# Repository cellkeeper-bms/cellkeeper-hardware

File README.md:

# CellKeeper BMS — v1.1

KiCad PCB design for the **CellKeeper Battery Management System**, a replacement BMS controller for battery packs using the isoSPI protocol. The main board fits the Tesla battery's penthouse: the pack's original harness, HV sense, shunt and BMB connectors plug into it, and it mounts on the original brackets.

Each ordered revision has a [release](https://github.com/cellkeeper-bms/cellkeeper-hardware/releases) with its Gerbers, JLCPCB BOM and CPL, schematic PDF, board PDF (3D views and 1:1 prints) and the enclosure print files. Rev 1.1 was ordered on 2026-10-28; work towards rev 1.2 is on the `rev1.2` branch.

## Overview

- **MCUs:** two Raspberry Pi RP2354B (dual Cortex-M33, 2 MB in-package flash): the main BMS controller and an independent supervisor, linked by UART. The supervisor also sees the isoSPI receive line and the E-stop input, and it alone enables the contactor drivers.
- **Current sensing:** TI INA228 (20-bit) on a galvanically isolated domain (ISO1540 I2C isolator, isolated 5 V DC-DC), also reading the shunt's temperature.
- **HV sensing:** 6 sense points (BAT±, LINK±, FC±) through 501:1 dividers into two ADS1115 ADCs: pack, link and output voltage, and the voltage across each contactor.
- **BMB communication:** transformer-isolated isoSPI master (SP3485 driver, AM26LV32 receiver, HM2113 transformer), Manchester-encoded by the RP2354's PIO.
- **CAN:** two ISO1050 interfaces: inverter CAN, isolated with its own DC-DC, on an RJ45 shared with the E-stop and aux lines; and inter-BMS CAN2 on a pass-through RJ45 pair (not isolated).
- **Contactors:** four low-side drivers (FC+, FC-, Link+, Link-): BSC0805LS MOSFETs and UCC27524 gate drivers, PWM'd by the firmware to economise the hold current. The contactor supply is sensed.
- **Supply:** 13–16 V logic and contactor inputs (separate, both sensed), TPS5430 5 V buck and 3.3 V LDO; chassis ground terminal.
- **HV battery:** 400 V nominal.
- **USB-C ×3:** BMS, supervisor, and HMI link. The HMI link is not for a computer: it powers an external ESP32 display (5 V 1 A) and carries its serial.
- **I/O:** E-stop input (optocoupler; jumper JP37 disables it), an extra opto input and two extra outputs, fast-charge contactor aux-contact inputs for weld detection, SX serial interface, and experimental PCS signals on jumpers.
- **Board revision** strap on GPIO47 (ADC7).

## Repository Contents

Three boards, each its own KiCad project. They share no copper: the hat and the precharge board
connect to the rest of the system by wires and lugs.

| Path | Description |
|------|-------------|
| `CellKeeper/` | Main controller board (`CellKeeper.kicad_pro`). Each ordered revision's Gerbers, BOM, CPL, schematic and board PDFs are on the [releases](https://github.com/cellkeeper-bms/cellkeeper-hardware/releases) page |
| `isoSPI-Hat/` | isoSPI hat for a Raspberry Pi Pico: SP3485 / AM26LV32 / HM2113 transformer to the BMB connector |
| `Precharge/` | Precharge board: six PTCs (three parallel strings of two) between M8 lugs, plus the HV system wiring diagram |
| `lib/` | Shared `CellKeeper_Local` symbol and footprint libraries and `CellKeeper.3dshapes` 3D models |
| `enclosure/` | 3D-printable case for the main board (build123d) |
| `graphics/` | Silkscreen artwork and README images |
| `python_scripts/` | README renders (`render_readme_images.py`), release files (`export_release_files.py`), 3D model generators |
| `docs/` | How to release a revision (`releasing.md`), README notes |

## Enclosure

A two-part printed case (base tray and lid) for the main board, generated by
`enclosure/cellkeeper_case.py`. It mounts in the penthouse on the original HVC brackets. The lid
carries the logo and connector labels, which can be printed as a contrasting-colour inlay, with
open tunnels over the LEDs. Ready-to-print STEP and STL files are attached to each
[release](https://github.com/cellkeeper-bms/cellkeeper-hardware/releases); running the script writes
them to `enclosure/output/print/`.
The board shows the case in KiCad's 3D viewer through the `ENC1` footprint.

## Safety

⚠️ This board interfaces with 400 V battery packs that can deliver **lethal** current. Only qualified personnel should work on high-voltage systems. This is a v1.1 development design — untested, no warranty, use at your own risk.

## Acknowledgments

- **Damien Maguire & Tom de Bree** — Original BATMan BMS software

## License

GPL-3.0 — see [LICENSE](LICENSE).

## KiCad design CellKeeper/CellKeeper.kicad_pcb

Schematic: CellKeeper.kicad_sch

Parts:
1/2V1, 3v1, 5V1: TP; BMS_Library__TestPoint_THTPad_D1.5mm_Drill1.0mm
BT5, BT6, BT7, BT8: ~100V Brick
C1, C14, C31: 680uF; Capacitor_THT__CP_Radial_D10.0mm_P5.00mm; Voltage 35V Polymer; JLCPCB Part # C46550429
C2, C10, C11, C13, C15, C16, C18, C22, C23, C28, C29, C30, C34, C35, C36, C54, C60, C73, C74, C89, C91, C104: 100nF; Capacitor_SMD__C_0603_1608Metric; JLCPCB Part # C14663
C3, C4, C6, C8, C17, C32, C66: 10uF; Capacitor_SMD__C_0805_2012Metric; Voltage 50V; JLCPCB Part # C440198
C5, C7, C12, C33, C37, C48, C49, C69: 22uF; Capacitor_SMD__C_0805_2012Metric; Voltage 25V X5R; JLCPCB Part # C45783
C9: 4.7uF; Capacitor_SMD__C_0603_1608Metric; JLCPCB Part # C19666
C19, C20, C41, C42, C67, C96, C97, C98, C99: 1uF; Capacitor_SMD__C_0603_1608Metric; JLCPCB Part # C15849
C21, C55, C116: 10uF; Capacitor_SMD__C_0805_2012Metric; Voltage 50V X5R; JLCPCB Part # C440198
C24, C25, C26, C27, C103: 100pF; Capacitor_SMD__C_0603_1608Metric; JLCPCB Part # C14858
C38, C43, C45, C52, C68, C72, C82, C87: 4.7u; RP2350_80QFN_minimal__C_0402_1005Metric_small_pads; JLCPCB Part # C23733
C39, C40, C70, C71: 15pF; Capacitor_SMD__C_0402_1005Metric; JLCPCB Part # C1548
C44, C46, C47, C50, C51, C53, C56, C58, C59, C61, C63, C65, C75, C83, C84, C85, C86, C88, C90, C92, C93, C100, C101, C102: 100n; Capacitor_SMD__C_0402_1005Metric; JLCPCB Part # C1525
C57, C105: 100n; Capacitor_SMD__C_0402_1005Metric; JLCPCB Part # C1525; not fitted
C62, C64, C76, C77, C78, C79, C80, C81: 100nf; Capacitor_SMD__C_0603_1608Metric; JLCPCB Part # C14663
C94, C95: 1nF; Capacitor_SMD__C_1206_3216Metric; JLCPCB Part # C9196
Cell1, Cell2, Cell3: Battery_Cell
D1, D2, D3, D4, D5, D6, D24, D25, D26, D28, D29, D30, D31: SMB6.8CA; Diode_SMD__D_SMB; JLCPCB Part # C78395
D7, D8, D14, D19, D32, D35, D36, D43, D48: Green; LED_SMD__LED_0805_2012Metric; JLCPCB Part # C2297
D9, D10, D27, D41, D46, D49: Red; LED_SMD__LED_0805_2012Metric; JLCPCB Part # C84256
D11, D12, D15, D16, D20, D23, D37, D38, D42, D44, D47, D50: SS54; Diode_SMD__D_SMA; JLCPCB Part # C22452
D13, D17, D22, D33, D34, D45: White; LED_SMD__LED_0805_2012Metric; JLCPCB Part # C34499
D18, D21, D39, D40: SMCJ33CA; Diode_SMD__D_SMC; JLCPCB Part # C224050
F3: Pyro Fuse
F4: 63A HV DC
FB1, FB3, FB5: 600R@100MHz; Inductor_SMD__L_0603_1608Metric_Pad1.05x0.95mm_HandSolder; JLCPCB Part # C1002
FB2: 120Ω@100MHz; Capacitor_SMD__C_0603_1608Metric; JLCPCB Part # C14709
FL1, FL2: SDCW3225S-2-102TF; BMS_Library__FILTER-SMD_4P-L3.2-W2.5-BL; JLCPCB Part # C192586
GND1: TP; BMS_Library__TestPoint_THTPad_D1.5mm_Drill1.0mm
GPIO44, GPIO45, GPIO46: TP; BMS_Library__TestPoint_THTPad_D1.5mm_Drill1.0mm
H1, H2, H7, H8: MountingHole_Pad; MountingHole__MountingHole_3.7mm; not fitted
H3, H4: MountingHole_Pad; MountingHole__MountingHole_5mm; not fitted
H5, H6: MountingHole_Pad
J1: WJ15EDGRC-3.81-04P-14-00A; BMS_Library__PhoenixContact_MC_1_5_4-G-3.81_1x04_P3.81mm_Ho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; JLCPCB Part # C7245
J2: T34008; BMS_Library__XFCN_T34008_M3_Terminal_Frame_PCB; JLCPCB Part # C481446
J3, J7: Screw_Terminal_01x04; BMS_Library__PhoenixContact_MC_1_5_4-G-3.81_1x04_P3.81mm_Ho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; JLCPCB Part # C7245; not fitted
J4, J5: 8P8C_LED_Shielded_x2; Connector_RJ__RJ45_HCTL_HC-RJ45-5JA-2-2-Y; JLCPCB Part # C3010546
J6: S44B-RAD1AK; BMS_Library__S44BRAD1AK; Mfr. # S44B-RAD1AK
J8, J16: Conn_01x03; Connector_PinHeader_2.54mm__PinHeader_1x03_P2.54mm_Vertical; not fitted
J9, J11, J19: USB_C_Receptacle_USB2.0_16P; BMS_Library__USB_C_Receptacle_HRO_TYPE-C-31-M-12; JLCPCB Part # C2765186
J10: 3.81P Screw Terminal; BMS_Library__PhoenixContact_MC_1_5_8-G-3.81_1x08_P3.81mm_Ho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; not fitted
J12, J22: Conn_02x10_Odd_Even; Connector_PinHeader_2.54mm__PinHeader_2x10_P2.54mm_Vertical; not fitted
J14: ZE05H-8DP-2H; BMS_Library__CONN_ZE05H-8DP-2H_HIR; MFR.Part # ZE05H-8DP-2H; JLCPCB Part # C17284895
J15: WJ15EDGRC-3.81-04P-14-00A; BMS_Library__PhoenixContact_MC_1_5_4-G-3.81_1x04_P3.81mm_Ho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; JLCPCB Part # C7245; not fitted
J17: OEM HV Sense Connector; BMS_Library__CONN_173864-1_TYC_Empty_Pins; MFR Part # 173864-1; JLCPCB Part # C573648
J18: 7.62mm Pitch Screw Terminal; Connector_Phoenix_GMSTB__PhoenixContact_GMSTBA_2_5_6-G-7_62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; not fitted
J20: OEM Connector; BMS_Library__CONN_SD-34912-001_02_MOL; MFR.Part # 349128020; JLCPCB Part # C587318
J21: 3.81P Screw Terminal; BMS_Library__PhoenixContact_MC_1_5_2-G-3.81_1x02_P3.81mm_Ho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; not fitted
JP3, JP4, JP7, JP8, JP9, JP12, JP13, JP14, JP16, JP17, JP18, JP19, JP20, JP21, JP22, JP23, JP24, JP27, JP28, JP29, JP30, JP31, JP32, JP33, JP34, JP35, JP37: 0r; BMS_Library__J_0603_jumper; JLCPCB Part # C21189; not fitted
JP5, JP6, JP10, JP11, JP15, JP36: 0r; BMS_Library__J_0603_jumper; JLCPCB Part # C21189
JP25, JP26, JP38, JP39: jumper-bridged; Jumper__SolderJumper-2_P1.3mm_Bridged_RoundedPad1.0x1.5mm
K5: Link Positive
K6: Link Negative
K7: FC Negative
K8: FC Positive
L1, L5: 6.8uh; Inductor_SMD__L_Changjiang_FXL0630; JLCPCB Part # C167221
L2, L3: 22uh 5.5A; Inductor_SMD__L_Changjiang_FXL1040; JLCPCB Part # C475917
L4, L6: 3.3uh; RP2350_80QFN_minimal__L_pol_2016; JLCPCB Part # C42411119
L7: Inverter
Q1, Q2, Q3, Q4: BSC0805LS; BMS_Library__TDSON-8_5x6_; JLCPCB Part # C534374
R1, R2, R11, R16, R29, R33, R35, R39, R40, R41, R96, R97, R98, R99, R100, R101, R140: 24k; Resistor_SMD__R_0603_1608Metric; JLCPCB Part # C23352
R3, R4, R13, R14, R15, R17, R19, R20, R21, R25, R28, R42, R50, R51, R52, R75, R84: 10k; Resistor_SMD__R_0603_1608Metric; JLCPCB Part # C25804
R5, R10, R18, R24, R34, R36, R151, R152: 100k; Resistor_SMD__R_0603_1608Metric; JLCPCB Part # C25803
R6: 25296nΩ
R7, R12, R37, R38: 33R; Resistor_SMD__R_0603_1608Metric; JLCPCB Part # C23140
R8, R9, R22, R23, R46, R47, R48, R49, R76, R133, R134, R141: 1k; Resistor_SMD__R_0603_1608Metric; JLCPCB Part # C21190
R26, R78, R155: 3.3k; Resistor_SMD__R_0402_1005Metric; JLCPCB Part # C25890
R27, R53, R55, R56, R74, R92, R94, R95, R129, R130, R131, R132, R135: 1k; Resistor_SMD__R_0402_1005Metric; JLCPCB Part # C11702
R30, R73, R86: 510r; Resistor_SMD__R_0603_1608Metric; JLCPCB Part # C23193
R31, R32: 120r; Resistor_SMD__R_1206_3216Metric; JLCPCB Part # C17909
R43, R44: 2.2k; Resistor_SMD__R_0603_1608Metric; JLCPCB Part # C4190
R45, R57, R66, R69, R72, R77, R79, R80, R81, R82, R83, R85, R89, R90, R138, R139, R143, R144, R153, R154: 5.1k; Resistor_SMD__R_0603_1608Metric; JLCPCB Part # C23186
R54, R68, R93, R126: 33r; Resistor_SMD__R_0402_1005Metric; JLCPCB Part # C25105
R58, R59, R60, R61, R62, R63, R64, R65: 18r
R67: 12.24R
R70, R71, R127, R128: 22R; Resistor_SMD__R_0402_1005Metric; JLCPCB Part # C25092
R87, R88: 220r; Resistor_SMD__R_0603_1608Metric; JLCPCB Part # C22962
R102, R103, R104, R105, R106, R107, R108, R109, R110, R111, R112, R113, R114, R115, R116, R117, R118, R119, R120, R121, R122, R123, R124, R125: 3M; Resistor_SMD__R_1206_3216Metric; JLCPCB Part # C488822
R136, R137: 47r; Resistor_SMD__R_0603_1608Metric; JLCPCB Part # C23182
R142: 100R; Resistor_SMD__R_0603_1608Metric; JLCPCB Part # C22775
R145, R146: 1M; Resistor_SMD__R_1206_3216Metric; JLCPCB Part # C17927
RevisionS1: TP; BMS_Library__TestPoint_THTPad_D1.5mm_Drill1.0mm
SW1, SW2, SW3, SW4: TS-1187A-B-A-B; Button_Switch_SMD__SW_Push_1P1T_XKB_TS-1187A; JLCPCB Part # C318884
TH1, TH2, TH3, TH4, TH5, TH6: B59451C1130B070; JLCPCB Part # C2762811
TP1, TP2, TP4, TP6, TP7, TP8, TP9, TP10, TP15, TP23, TP24, TP25, TP34, TP35, TP36, TP37, TP43, TP44, TP45: TestPoint_2Pole; BMS_Library__TestPoint_2Pads_Pitch2.54mm_Pad1.5_Drill1.0mm
TP3, TP5, TP11, TP12, TP13, TP14, TP16, TP17, TP18, TP19, TP20, TP21, TP22, TP26, TP27, TP28, TP29, TP30, TP31, TP32, TP33, TP38, TP39, TP40, TP41, TP49: TP; BMS_Library__TestPoint_THTPad_D1.5mm_Drill1.0mm
TP42: TestPoint_2Pole; BMS_Library__TestPoint_2Pads_Pitch2.54mm_Pad1.5_Drill1.0mm; not fitted
TR1: HM2113ZNLT; BMS_Library__HM2113ZNLT; JLCPCB Part # C5730533
U1, U11: UCC27524DR; Package_SO__SOIC-8_3.9x4.9mm_P1.27mm; JLCPCB Part # C465729
U3: TPS5430DDAR; Package_SO__TI_SO-PowerPAD-8_ThermalVias; LCSC Part C9864
U4, U15: F0505S-1WR3; BMS_Library__H0505S-1WR2; JLCPCB Part # C7465182
U5, U10: ISO1050DUB; Package_SO__SOP-8_6.62x9.15mm_P2.54mm; LCSC Part # C16428
U6, U7, U8, U9, U12, U13: LTV-217-B-G; Package_SO__SSOP-4_4.4x2.6mm_P1.27mm; JLCPCB Part # C115450
U14, U20: RP2354B; RP2350_80QFN_minimal__RP2350-QFN-80-1EP_10x10_P0.4mm_EP3.4x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; JLCPCB Part # C39843328
U16: ISO1540; Package_SO__SOIC-8_3.9x4.9mm_P1.27mm; JLCPCB Part # C179739
U17: INA228; Package_SO__TSSOP-10_3x3mm_P0.5mm; JLCPCB Part # C5214669
U18, U19: ADS1115; Package_SO__TSSOP-10_3x3mm_P0.5mm; LCSC Part # C37593
U21: SP3485EN-L/TR; Package_SO__SOIC-8_3.9x4.9mm_P1.27mm; JLCPCB Part # C8963
U22: AM26LV32EIDR; Package_SO__SOIC-16_3.9x9.9mm_P1.27mm; JLCPCB Part # C527448
U23, U24: W25Q16JVUXIQ; Winbond_USON-8-1EP_3x2mm_P0.5mm_EP0.2x1.6mm; JLCPCB Part # C2843335; not fitted
U25, U26: TLV1117LV33DCYR; Package_TO_SOT_SMD__SOT-223-3_TabPin2; JLCPCB Part # C15578
Y1, Y2: ABM8-272-T3; Crystal__Crystal_SMD_3225-4Pin_3.2x2.5mm; JLCPCB Part # C20625731

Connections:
3.3V Sense: C22.2, R20.2, R21.1, U14.49 (GPIO40_ADC0)
5V Sense: C36.2, R41.2, R42.1, U14.52 (GPIO41_ADC1)
+1V1: C43.1, C44.1, C46.1, C47.1, L4.1, U14.10 (DVDD), U14.32 (DVDD), U14.51 (DVDD), U14.65 (VREG_FB)
+1V1_2: C72.1, C75.1, C83.1, C84.1, L6.1, U20.10 (DVDD), U20.32 (DVDD), U20.51 (DVDD), U20.65 (VREG_FB)
+3.3V: C9.2, C10.1, C11.1, C38.1, C50.1, C51.1, C53.1, C56.1, C57.1, C58.1, C59.1, C61.1, C63.1, C65.1, C66.2, C68.1, C85.1, C86.1, C88.1, C89.1, C90.1, C91.2, C92.1, C93.1, C100.1, C101.1, C102.1, C105.1, D7.2 (A), D9.2 (A), D41.2 (A), D43.2 (A), FB5.1, J3.1, J12.5, J12.7, J12.9, J22.5, J22.7, J22.9, JP35.2, R2.1, R4.1, R15.1, R20.1, R28.1, R29.1, R54.2, R57.1, R66.1, R68.2, R75.1, R89.1, R90.1, R93.2, R126.2, R135.1, TP4.2, U5.1 (VCC1), U6.4, U7.4, U10.1 (VCC1), U12.4, U13.4, U14.5 (IOVDD), U14.15 (IOVDD), U14.24 (IOVDD), U14.29 (IOVDD), U14.41 (IOVDD), U14.50 (IOVDD), U14.60 (IOVDD), U14.64 (VREG_VIN), U14.68 (USB_OTP_VDD), U14.69 (QSPI_IOVDD), U14.76 (IOVDD), U16.1 (VCC1), U20.5 (IOVDD), U20.15 (IOVDD), U20.24 (IOVDD), U20.29 (IOVDD), U20.41 (IOVDD), U20.50 (IOVDD), U20.60 (IOVDD), U20.64 (VREG_VIN), U20.68 (USB_OTP_VDD), U20.69 (QSPI_IOVDD), U20.76 (IOVDD), U21.8 (VCC), U22.4 (G), U22.16 (VDD), U23.8 (VCC), U24.8 (VCC), U25.2 (VO)
+3.3VSen: 3v1.1 (1_1), C67.2, C73.2, C74.2, FB5.2, R87.1, U18.8 (VDD), U19.1 (ADDR), U19.8 (VDD)
+5V: C2.2, C3.2, C7.2, C18.2, C29.2, C31.1, C32.2, C33.2, C37.2, C41.2, C42.2, C48.2, D50.2 (A), FB2.2, J12.1, J12.3, J22.1, J22.3, L1.2, L3.1, L5.2, R26.1, R35.1, R41.1, TP9.2, U1.6 (V_{DD}), U10.8 (VCC2), U11.6 (V_{DD}), U12.1, U13.1
+LDO_IN: C5.2, D44.1 (K), D47.1 (K), D50.1 (K), U25.3 (VI)
/Blue: J4.4, JP15.2, JP16.1, JP18.1
/Brown: J4.8, JP19.2, JP20.1, JP23.1
/CAN2 H: C26.2, D30.2 (A2), FL2.2, J5.4, J5.16, R32.2, TP8.2
/CAN2 L: C27.1, D31.1 (A1), FL2.3, J5.5, J5.17, JP5.1, TP8.1
/CAN 5V: 5V1.1 (1_1), C28.2, FB1.2, R22.2, R30.1, R33.1, R43.2, U5.8 (VCC2)
/CAN H: C24.2, D28.2 (A2), FL1.2, JP3.1, JP7.1, JP9.1, JP13.1, JP15.1, JP19.1, JP21.1, JP27.1, JP36.1, TP7.2
/CAN L: C25.1, D29.1 (A1), FL1.3, JP4.2, JP8.2, JP10.2, JP14.2, JP16.2, JP20.2, JP22.2, JP28.2, R31.1, TP7.1
/Contactor_Input: D1.2 (A2), D11.2 (A), D12.2 (A), J1.3
/FC-CTR-NEG-AUX-D: J6.17, J7.2, R47.1
/FC-CTR-POS-AUX-D: J6.18, J7.1, R46.1
/FC-Neg-Jumper: C35.2, D36.1 (K), D38.2 (A), D40.2 (A2), JP25.1 (A), JP26.1 (A), Q4.5 (D)
/FC-Pos-Jumper: C13.2, D14.1 (K), D16.2 (A), D18.2 (A2), JP38.1 (A), JP39.1 (A), Q1.5 (D)
/GPIO0: R74.2, U14.77 (GPIO0)
/GPIO25: R85.1, U14.26 (GPIO25)
/GPIO44_ADC4: GPIO44.1 (1_1), U14.55 (GPIO44_ADC4)
/GPIO45_ADC5: GPIO45.1 (1_1), U14.56 (GPIO45_ADC5)
/GPIO46_ADC6: GPIO46.1 (1_1), U14.57 (GPIO46_ADC6)
/GPIO47_ADC7: R75.2, R76.1, RevisionS1.1 (1_1), U14.58 (GPIO47_ADC7)
/Grn: J4.6, JP7.2, JP8.1, JP11.1
/Logic_Input: D4.2 (A2), D15.2 (A), J1.4, R151.2
/MCU2_GPIO0: R135.2, U20.77 (GPIO0)
/MCU2_GPIO1: R131.2, U20.78 (GPIO1)
/MCU2_GPIO2: R132.2, U20.79 (GPIO2)
/MCU2_GPIO4: J22.4, U20.1 (GPIO4)
/MCU2_GPIO5: J22.6, U20.2 (GPIO5)
/MCU2_GPIO6: J22.8, R133.1, U20.3 (GPIO6)
/MCU2_GPIO7: J22.10, U20.4 (GPIO7)
/MCU2_GPIO8: J22.12, R134.1, U20.6 (GPIO8)
/MCU2_GPIO9: J22.14, U20.7 (GPIO9)
/MCU2_GPIO10: J22.16, U20.8 (GPIO10)
/MCU2_GPIO12: J22.20, U20.11 (GPIO12)
/MCU2_GPIO13: U20.12 (GPIO13)
/MCU2_GPIO14: R140.1, R141.1, U20.13 (GPIO14)
/MCU2_GPIO15: U20.14 (GPIO15)
/MCU2_GPIO16: U20.16 (GPIO16)
/MCU2_GPIO17: U20.17 (GPIO17)
/MCU2_GPIO18: U20.18 (GPIO18)
/MCU2_GPIO19: U20.19 (GPIO19)
/MCU2_GPIO20: U20.20 (GPIO20)
/MCU2_GPIO21: U20.21 (GPIO21)
/MCU2_GPIO22: U20.22 (GPIO22)
/MCU2_GPIO23: U20.23 (GPIO23)
/MCU2_GPIO24: U20.25 (GPIO24)
/MCU2_GPIO25: R143.1, U20.26 (GPIO25)
/MCU2_GPIO26: U20.27 (GPIO26)
/MCU2_GPIO27: U20.28 (GPIO27)
/MCU2_GPIO33: U20.42 (GPIO33)
/MCU2_GPIO34: U20.43 (GPIO34)
/MCU2_GPIO35: U20.44 (GPIO35)
/MCU2_GPIO36: U20.45 (GPIO36)
/MCU2_GPIO37: U20.46 (GPIO37)
/MCU2_GPIO38: R129.2, U20.47 (GPIO38)
/MCU2_GPIO39: R130.2, U20.48 (GPIO39)
/Orange: J4.2, JP21.2, JP22.1, JP24.1
/PH: C16.1, D23.1 (K), L3.2, U3.8 (PH)
/RUN: R56.2, SW2.2, TP14.1 (1_1)
/SWCLK: J8.1, U14.33 (SWCLK)
/SWD: J8.3, U14.34 (SWD)
/Serial API 5V Diode: D42.1 (K), J9.A4 (VBUS), J9.A9 (VBUS), J9.B4 (VBUS), J9.B9 (VBUS), TP13.1 (1_1)
/Serial API RX: J9.A7 (D-), J9.B7 (D-), R48.1, R50.2, TP10.1
/Serial API TX: J9.A6 (D+), J9.B6 (D+), R49.1, TP10.2
/USB2_D+: J19.A6 (D+), J19.B6 (D+), R127.1, TP39.1 (1_1)
/USB2_D-: J19.A7 (D-), J19.B7 (D-), R128.1, TP40.1 (1_1)
/USB_D+: J11.A6 (D+), J11.B6 (D+), R70.1, TP20.1 (1_1)
/USB_D-: J11.A7 (D-), J11.B7 (D-), R71.1, TP21.1 (1_1)
/VREG2_AVDD: C82.1, R93.1, U20.61 (VREG_AVDD)
/VREG2_LX: L6.2, U20.63 (VREG_LX)
/VREG_AVDD: C45.1, R54.1, U14.61 (VREG_AVDD)
/VREG_LX: L4.2, U14.63 (VREG_LX)
/V_cont1: C8.2, D11.1 (K), D12.1 (K), L2.2
/Wht-Blue: J4.5, JP9.2, JP10.1, JP12.1
/Wht-Brown: J4.7, JP13.2, JP14.1, JP17.1
/Wht-Grn: J4.3, JP3.2, JP4.1, JP6.1
/Wht-Org: J4.1, JP27.2, JP28.1, JP29.1
/iso+: C96.1, C99.1, C103.2, R136.2, R142.1, TP42.1, TR1.1 (TD-)
/iso-: C97.1, C98.1, C103.1, R137.2, R142.2, TP42.2, TR1.3 (TD+)
Batt Negative: J17.1, J18.6, R121.2
Batt Positive: J17.10, J18.1, R120.2
C FC-Neg (GND): J6.37, J10.2, JP25.2 (B), JP26.2 (B)
C FC-Pos (GND): J6.36, J10.4, JP38.2 (B), JP39.2 (B)
C Neg (GND): C34.2, D35.1 (K), D37.2 (A), D39.2 (A2), J6.42, J10.6, Q3.5 (D)
C Pos (GND): C15.2, D19.1 (K), D20.2 (A), D21.2 (A2), J6.41, J10.8, Q2.5 (D)
CAN2 Rx: D8.1 (K), J12.6, TP2.1, U10.2 (RXD), U14.2 (GPIO5)
CAN2 Tx: D10.1 (K), J12.4, TP2.2, U10.3 (TXD), U14.1 (GPIO4)
CAN Rx: R1.2, TP1.1, U5.2 (RXD), U14.20 (GPIO20)
CAN Tx: R3.2, TP1.2, U5.3 (TXD), U14.19 (GPIO19)
CTR-FC-NEG: R83.1, U11.4 (INB), U14.14 (GPIO15)
CTR-FC-Pos: R82.1, U1.4 (INB), U14.16 (GPIO16)
CTR-LNK-NEG: R81.1, U11.2 (INA), U14.17 (GPIO17)
CTR-LNK-POS: R77.1, U1.2 (INA), U14.18 (GPIO18)
CTR_EN: R141.2, R144.1, U1.1 (ENA), U1.8 (ENB), U11.1 (ENA), U11.8 (ENB)
Emergency Stop: J12.18, J22.18, R13.2, U6.3, U14.9 (GPIO11), U20.9 (GPIO11)
Extra Input: J12.20, R14.2, U7.3, U14.11 (GPIO12)
Extra Output 1: R8.1, U14.12 (GPIO13)
Extra Output 2: R9.1, U14.13 (GPIO14)
FC Negative: J17.4, J18.4, R123.2
FC Positive: J17.7, J18.3, R122.2
FC-CTR-NEG-AUX: J12.16, R52.2, U13.3, U14.8 (GPIO10)
FC-CTR-POS-AUX: J12.14, R51.2, U12.3, U14.7 (GPIO9)
GND: C1.2, C2.1, C3.1, C4.1, C5.1, C6.1, C7.1, C8.1, C9.1, C10.2, C11.2, C12.1, C13.1, C14.2, C15.1, C17.1, C18.1, C22.1, C23.1, C26.1, C27.2, C29.1, C30.1, C31.2, C32.1, C33.1, C34.1, C35.1, C36.1, C37.1, C38.2, C39.2, C40.2, C43.2, C44.2, C45.2, C46.2, C47.2, C48.1, C49.1, C50.2, C51.2, C52.2, C53.2, C56.2, C57.2, C58.2, C59.2, C61.2, C63.2, C65.2, C66.1, C67.1, C68.2, C69.1, C70.2, C71.2, C72.2, C73.1, C74.1, C75.2, C82.2, C83.2, C84.2, C85.2, C86.2, C87.2, C88.2, C89.2, C90.2, C91.1, C92.2, C93.2, C100.2, C101.2, C102.2, C104.1, C105.2, D3.1 (A1), D6.1 (A1), D13.1 (K), D17.1 (K), D18.1 (A1), D21.1 (A1), D22.1 (K), D23.2 (A), D26.1 (A1), D30.1 (A1), D31.2 (A2), D34.1 (K), D39.1 (A1), D40.1 (A1), D46.1 (K), D48.1 (K), D49.1 (K), GND1.1 (1_1), J1.1, J1.2, J2.1 (Pin_1_1), J3.4, J5.3, J5.6, J5.15, J5.18, J5.SH, J6.3, J6.4, J6.30, J7.3, J7.4, J8.2, J9.A1 (GND), J9.A12 (GND), J9.B1 (GND), J9.B12 (GND), J9.SH (SHIELD), J11.A1 (GND), J11.A12 (GND), J11.B1 (GND), J11.B12 (GND), J11.SH (SHIELD), J12.11, J12.13, J12.15, J12.17, J12.19, J16.2, J19.A1 (GND), J19.A12 (GND), J19.B1 (GND), J19.B12 (GND), J19.SH (SHIELD), J22.11, J22.13, J22.15, J22.17, J22.19, Q1.1 (S), Q1.2 (S), Q1.3 (S), Q2.1 (S), Q2.2 (S), Q2.3 (S), Q3.1 (S), Q3.2 (S), Q3.3 (S), Q4.1 (S), Q4.2 (S), Q4.3 (S), R5.1, R10.1, R13.1, R14.1, R19.2, R21.2, R25.2, R27.2, R34.1, R36.1, R42.2, R51.1, R52.1, R74.1, R76.2, R77.2, R79.1, R80.1, R81.2, R82.2, R83.2, R88.2, R138.1, R139.1, R144.2, R146.1, R153.2, R154.2, SW1.1, SW2.1, SW3.1, SW4.1, TP3.1 (1_1), TP4.1, TP9.1, TP11.1 (1_1), TP16.1 (1_1), TP19.1 (1_1), TP23.1, TP24.1, TP38.1 (1_1), TP43.1, TP44.1, U1.3 (GND), U3.6 (GND), U3.9 (PowerPAD), U4.2 (-Vin), U5.4 (GND1), U8.2, U9.2, U10.4 (GND1), U10.5 (GND2), U11.3 (GND), U14.62 (VREG_PGND), U14.81 (GND), U15.2 (-Vin), U16.4 (GND1), U18.1 (ADDR), U18.3 (GND), U19.3 (GND), U20.62 (VREG_PGND), U20.81 (GND), U21.2 (~RE), U21.5 (GND), U22.8 (GND), U22.12 (~G), U23.4 (GND), U24.4 (GND), U25.1 (GND), Y1.2, Y1.4, Y2.2, Y2.4
GND CAN: C21.1, C24.1, C25.2, C28.1, D28.1 (A1), D29.2 (A2), D33.1 (K), J4.19, J4.SH, JP6.2, JP11.2, JP12.2, JP17.2, JP18.2, JP23.2, JP24.2, JP29.2, JP37.2, R30.2, TP5.1 (1_1), U4.5 (-Vout), U5.5 (GND2)
GND Shunt NTC -: C54.1, C55.1, C60.1, C64.1, C116.1, D45.1 (K), J14.1, J14.3, J15.2, R73.2, R86.2, TP17.1 (1_1), U15.5 (-Vout), U16.5 (GND2), U17.1 (A1), U17.2 (A0), U17.7 (GND), U26.1 (GND)
HMI Serial RX: R48.2, R130.1, U14.48 (GPIO39)
HMI Serial TX: R45.2, R49.2, R129.1, U14.47 (GPIO38)
I2C SCL Shunt: R57.2, TP15.2, U14.21 (GPIO21), U16.3 (SCL1)
I2C SCL Vsense: R90.2, TP25.2, U14.23 (GPIO23), U18.10 (SCL), U19.10 (SCL)
I2C SDA Shunt: R66.2, TP15.1, U14.25 (GPIO24), U16.2 (SDA1)
I2C SDA Vsense: R89.2, TP25.1, U14.22 (GPIO22), U18.9 (SDA), U19.9 (SDA)
IsoSPI RX Debug: TP24.2, U14.39 (GPIO31)
IsoSPI RX Debug 2: TP43.2, U20.39 (GPIO31)
IsoSPI RX H: TP35.1, U14.36 (GPIO28), U20.36 (GPIO28), U22.5 (2Y)
IsoSPI RX L: TP35.2, U14.37 (GPIO29), U20.37 (GPIO29), U22.3 (1Y)
IsoSPI TX Data: TP34.2, U14.28 (GPIO27), U21.4 (DI)
IsoSPI TX En: TP34.1, U14.27 (GPIO26), U21.3 (DE)
IsoSPI+: J20.1, J21.1, TR1.4 (TX+)
IsoSPI-: J20.2, J21.2, TR1.6 (TX-)
Link Negative: J17.13, J18.5, R124.2
Link Positive: J17.22, J18.2, R125.2
MAIN-SUP TX/RX: R131.1, TP36.1, U14.79 (GPIO2)
MAX RX: J12.8, R133.2, U14.3 (GPIO6), U22.13 (4Y)
unnamed: BT5.1 (+), K5.14
unnamed: BT5.2 (-), BT6.1 (+)
unnamed: BT6.2 (-), R6.1
unnamed: BT7.1 (+), F3.1
unnamed: BT7.2 (-), BT8.1 (+)
unnamed: BT8.2 (-), K6.14
unnamed: C19.1, J4.20, J4.21, JP37.1, U6.2
unnamed: C19.2, R22.1, U6.1
unnamed: C20.1, J4.14, J4.23, U7.2
unnamed: C20.2, R23.1, U7.1
unnamed: C40.1, R53.2, Y1.3
unnamed: C41.1, R46.2, U12.2
unnamed: C42.1, R47.2, U13.2
unnamed: C71.1, R92.2, Y2.3
unnamed: C94.1, TP37.2
unnamed: C95.1, TP37.1
unnamed: Cell1.1 (+), R58.1, R59.1
unnamed: Cell1.2 (-), Cell2.1 (+), R60.1, R61.1
unnamed: Cell2.2 (-), Cell3.1 (+), R62.1, R63.1
unnamed: Cell3.2 (-), R64.1, R65.1
unnamed: D1.1 (A1), D2.2 (A2)
unnamed: D2.1 (A1), D3.2 (A2)
unnamed: D4.1 (A1), D5.2 (A2)
unnamed: D5.1 (A1), D6.2 (A2)
unnamed: D7.1 (K), R1.1
unnamed: D8.2 (A), R2.2
unnamed: D9.1 (K), R3.1
unnamed: D10.2 (A), R4.2
unnamed: D13.2 (A), R151.1
unnamed: D14.2 (A), R11.2
unnamed: D17.2 (A), R15.2
unnamed: D19.2 (A), R16.2
unnamed: D22.2 (A), R152.1
unnamed: D24.1 (A1), D25.2 (A2)
unnamed: D25.1 (A1), D26.2 (A2)
unnamed: D27.2 (A), R28.2
unnamed: D32.2 (A), R29.2
unnamed: D33.2 (A), R33.2
unnamed: D34.2 (A), R35.2
unnamed: D35.2 (A), R39.2
unnamed: D36.2 (A), R40.2
unnamed: D41.1 (K), R45.1
unnamed: D42.2 (A), FB2.1
unnamed: D43.1 (K), R50.1
unnamed: D44.2 (A), J11.A4 (VBUS), J11.A9 (VBUS), J11.B4 (VBUS), J11.B9 (VBUS), R78.2, TP22.1 (1_1)
unnamed: D45.2 (A), R17.2
unnamed: D46.2 (A), R85.2
unnamed: D47.2 (A), J19.A4 (VBUS), J19.A9 (VBUS), J19.B4 (VBUS), J19.B9 (VBUS), R155.2, TP41.1 (1_1)
unnamed: D48.2 (A), R140.2
unnamed: D49.2 (A), R143.2
unnamed: F3.2, R6.4
unnamed: H5.1, K6.13, K7.14, TH1.1, TH2.1, TH3.1
unnamed: H6.1, K7.13, L7.2, TH4.2, TH5.2, TH6.2
unnamed: J4.13, R23.2, R44.2
unnamed: J4.15, U9.4
unnamed: J4.16, U8.3
unnamed: J4.17, U8.4
unnamed: J4.18, U9.3
unnamed: J4.22, R43.1
unnamed: J4.24, R44.1
unnamed: J6.1, JP30.2
unnamed: J6.2, JP31.2
unnamed: J6.5, JP32.2
unnamed: J6.6, JP33.2
unnamed: J6.15, JP34.2
unnamed: J6.29, JP35.1
unnamed: J11.A5 (CC1), R79.2
unnamed: J11.B5 (CC2), R80.2
unnamed: J16.1, U20.33 (SWCLK)
unnamed: J16.3, U20.34 (SWD)
unnamed: J19.A5 (CC1), R138.2
unnamed: J19.B5 (CC2), R139.2
unnamed: JP5.2, R32.1
unnamed: JP36.2, R31.2
unnamed: K5.13, K8.14
unnamed: K8.13, L7.1
unnamed: Q1.4 (G), R7.2
unnamed: Q2.4 (G), R12.2
unnamed: Q3.4 (G), R37.2
unnamed: Q4.4 (G), R38.2
unnamed: R8.2, U8.1
unnamed: R9.2, U9.1
unnamed: R55.2, SW1.2, TP12.1 (1_1)
unnamed: R58.2, R59.2
unnamed: R60.2, R61.2, R67.2
unnamed: R62.2, R63.2, R67.1
unnamed: R64.2, R65.2
unnamed: R94.2, SW3.2, TP26.1 (1_1)
unnamed: R95.2, SW4.2, TP30.1 (1_1)
unnamed: R102.2, R108.1
unnamed: R103.2, R109.1
unnamed: R104.2, R110.1
unnamed: R105.2, R111.1
unnamed: R106.2, R112.1
unnamed: R107.2, R113.1
unnamed: R108.2, R114.1
unnamed: R109.2, R115.1
unnamed: R110.2, R116.1
unnamed: R111.2, R117.1
unnamed: R112.2, R118.1
unnamed: R113.2, R119.1
unnamed: R114.2, R120.1
unnamed: R115.2, R121.1
unnamed: R116.2, R122.1
unnamed: R117.2, R123.1
unnamed: R118.2, R124.1
unnamed: R119.2, R125.1
unnamed: R145.1, R146.2
unnamed: TH1.2, TH4.1
unnamed: TH2.2, TH5.1
unnamed: TH3.2, TH6.1
unnamed: C104.2, TR1.2 (C_TD)
unnamed: R145.2, TR1.5 (C_TX)
unnamed: R10.2, R12.1, U1.7 (OUTA)
unnamed: R5.2, R7.1, U1.5 (OUTB)
unnamed: C16.2, U3.1 (BOOT)
unnamed: R26.2, R27.1, U3.4 (VSENSE)
unnamed: C12.2, L1.1, U4.1 (+Vin)
unnamed: C21.2, FB1.1, U4.7 (+Vout)
unnamed: FL1.1, U5.7 (CANH)
unnamed: FL1.4, U5.6 (CANL)
unnamed: FL2.1, U10.7 (CANH)
unnamed: FL2.4, U10.6 (CANL)
unnamed: R34.2, R37.1, U11.7 (OUTA)
unnamed: R36.2, R38.1, U11.5 (OUTB)
unnamed: C52.1, R68.1, U14.59 (ADC_AVDD)
unnamed: U14.71 (QSPI_SCLK), U23.6 (CLK)
unnamed: U14.72 (QSPI_SD0), U23.5 (DI/IO_{0})
unnamed: U14.74 (QSPI_SD1), U23.2 (DO/IO_{1})
unnamed: U14.73 (QSPI_SD2), U23.3 (~WP/IO_{2})
unnamed: U14.70 (QSPI_SD3), U23.7 (~HOLD/~RESET/IO_{3})
unnamed: R55.1, U14.75 (QSPI_SS), U23.1 (~CS)
unnamed: R56.1, U14.35 (RUN)
unnamed: R71.2, U14.66 (USB_DM)
unnamed: R70.2, U14.67 (USB_DP)
unnamed: C39.1, U14.30 (XIN), Y1.1
unnamed: R53.1, U14.31 (XOUT)
unnamed: C49.2, L5.1, U15.1 (+Vin)
unnamed: C55.2, FB3.1, U15.7 (+Vout)
unnamed: R72.2, U16.6 (SCL2), U17.5 (SCL)
unnamed: R69.2, U16.7 (SDA2), U17.4 (SDA)
unnamed: C76.2, R96.1, R102.1, TP31.1 (1_1), U18.4 (AIN0), U19.6 (AIN2)
unnamed: C77.1, R97.2, R103.1, TP29.1 (1_1), U18.5 (AIN1)
unnamed: C78.2, R98.1, R104.1, TP33.1 (1_1), U18.6 (AIN2), U19.5 (AIN1)
unnamed: C79.1, R99.1, R105.1, TP27.1 (1_1), U18.7 (AIN3)
unnamed: C80.2, R100.1, R106.1, TP32.1 (1_1), U19.4 (AIN0)
unnamed: C81.1, R101.1, R107.1, TP28.1 (1_1), U19.7 (AIN3)
unnamed: C87.1, R126.1, U20.59 (ADC_AVDD)
unnamed: U20.71 (QSPI_SCLK), U24.6 (CLK)
unnamed: U20.72 (QSPI_SD0), U24.5 (DI/IO_{0})
unnamed: U20.74 (QSPI_SD1), U24.2 (DO/IO_{1})
unnamed: U20.73 (QSPI_SD2), U24.3 (~WP/IO_{2})
unnamed: U20.70 (QSPI_SD3), U24.7 (~HOLD/~RESET/IO_{3})
unnamed: R94.1, U20.75 (QSPI_SS), U24.1 (~CS)
unnamed: R95.1, U20.35 (RUN)
unnamed: R128.2, U20.66 (USB_DM)
unnamed: R127.2, U20.67 (USB_DP)
unnamed: C70.1, U20.30 (XIN), Y2.1
unnamed: R92.1, U20.31 (XOUT)
unnamed: R136.1, U21.6 (A)
unnamed: R137.1, U21.7 (B)
unnamed: C96.2, U22.2 (1A)
unnamed: C97.2, U22.1 (1B)
unnamed: C98.2, U22.6 (2A)
unnamed: C99.2, U22.7 (2B)
unnamed: C94.2, U22.14 (4A)
unnamed: C95.2, U22.15 (4B)
PCS Charge: JP34.1, U14.46 (GPIO37)
PCS DCDC: JP30.1, U14.42 (GPIO33)
PCS Enable: JP31.1, U14.45 (GPIO36)
PCS IPC CAN RX: JP32.1, U14.44 (GPIO35)
PCS IPC CAN TX: JP33.1, U14.43 (GPIO34)
SUP-MAIN TX/RX: R132.1, TP36.2, U14.78 (GPIO1)
SX Serial RX: D32.1 (K), J3.3, J12.12, R134.2, TP6.2, U14.6 (GPIO8)
SX Serial TX: D27.1 (K), J3.2, J12.10, TP6.1, U14.4 (GPIO7)
Shunt Midpoint: J14.8
Shunt NTC +: C64.2, J14.7, J15.1, R84.1, U17.8 (Vbus)
Shunt Passive +: J14.6
Shunt Sense +: C62.2, J14.5, J15.3, TP45.2, U17.10 (Vin+)
Shunt Sense -: C62.1, J14.4, J15.4, TP45.1, U17.9 (Vin-)
Shunt_3V3: C54.2, C60.2, C116.2, R17.1, R69.1, R72.1, R84.2, TP49.1 (1_1), U16.8 (VCC2), U17.6 (VS), U26.2 (VO)
Shunt_5V: FB3.2, R73.1, R86.1, TP18.1 (1_1), U26.3 (VI)
Snooper Debug: TP23.2, U14.40 (GPIO32)
Snooper Debug 2: TP44.2, U20.40 (GPIO32)
VBUS Detect USB1: J12.2, R78.1, R153.1, U14.80 (GPIO3)
VBUS Detect USB2: J22.2, R154.1, R155.1, U20.80 (GPIO3)
VContactor Sense: C30.2, R24.1, R25.1, U14.54 (GPIO43_ADC3)
VSenHalf: 1/2V1.1 (1_1), C69.2, C76.1, C77.2, C78.1, C79.2, C80.1, C81.2, R87.2, R88.1, R96.2, R97.1, R98.2, R99.2, R100.2, R101.2
V_{Contactor}: C14.1, C17.2, D16.1 (K), D20.1 (K), D24.2 (A2), D37.1 (K), D38.1 (K), J6.33, J6.34, J6.35, J6.43, J10.1, J10.3, J10.5, J10.7, L2.1, R11.1, R16.1, R24.2, R39.1, R40.1, R152.2
V_{in}: C1.1, C4.2, C6.2, D15.1 (K), R18.2, U3.7 (VIN)
Vin Logic Sense: C23.2, R18.1, R19.1, U14.53 (GPIO42_ADC2)

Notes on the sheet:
all JLC basic components
Overall HV Battery System Diagram
3.3V 1A LDO Supply
GPIO3 - GPIO12 on NC header
external NC switch for estop, or jumper to disable.
Not tested as of now
I2C ADDR: 0x49
Aux Input 3-5V limited by resistor dissipation for higher input voltage use external series resistor
FC Negative Contactor
Would be cool if it alternates with main
BMB side xfmr center tap has no connection reference to ground to prevent ESD
Use 3v3 so no logic translation necessary.
TX must be on this pin
GND to battery chassis
unused inputs left floating - internal bias
3A max output - 3.3V draws from this rail
1.122V
1.52V
PTC max current ~10A Under 1S charge time expected
100k input impedance 0.14mA typical ADC usage
Gate driver has internal 200k pullup, 2x in parallel = 100k pullup must pull down to always start in off state.
DIY connector
MCU Identification
In tesla packs the shunt is at the mid point of the pack and always live!
second ADS1115: 0-1 linkneg - outpos 0-3 linkneg - linkpos <- link voltage 1-3 outpos - linkpos <- voltage across FC pos contactor 2-3 batpos - linkpos <- voltage across battery pos contactor
Supervisor MCU
5V powers exteral ESP32 LCD also
FC Positive Contactor
Cells to Positive Link Contactor
close to MCU
Aux contacts inside of the FC contactors used to check for welding with or without energizing
Extra GPIO
API TTL RS232 HMI Interface
Redundant connectors
Galvanically Isolated Area
isoSPI Transceiver
Inductor Alternate Parts (untested) APS201610M3R3F C48783272 MHT201610SG-3R3M H C49435043
Shunt Current Sense
Redundant connectors only one used at a time
3.77V

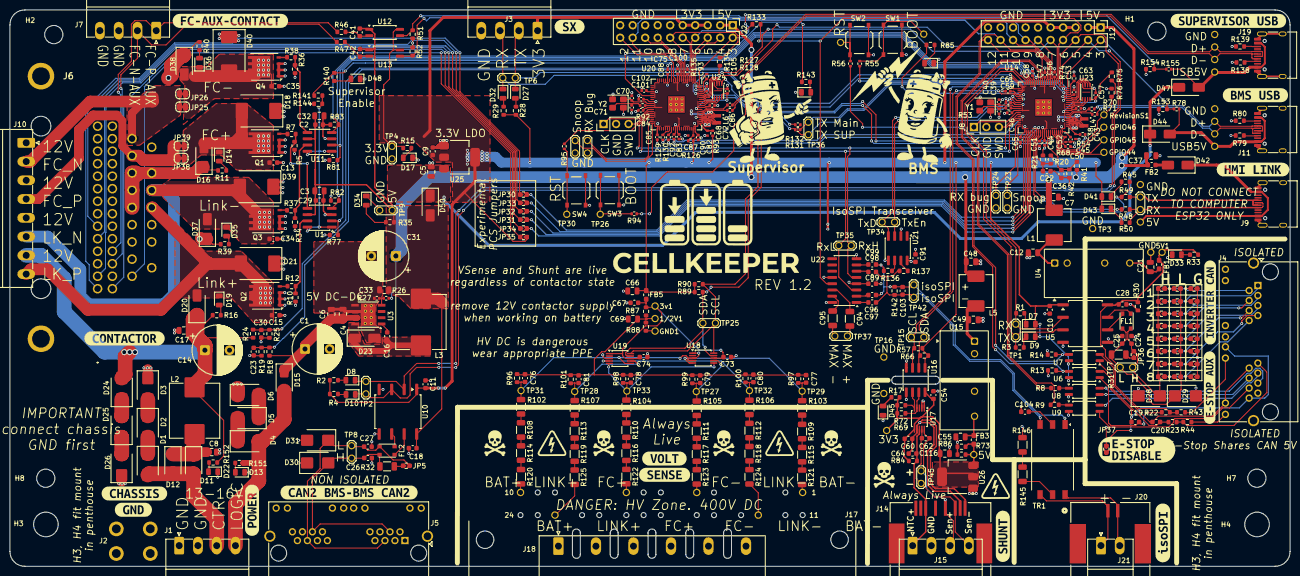
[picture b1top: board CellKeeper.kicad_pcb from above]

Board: 4 copper layers, 260.0 x 113.0 mm, 480 parts (0 on the bottom side), 277 nets.

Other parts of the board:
ENC1: CellKeeper_Enclosure
kibuzzard-6A455E05: G***; kibuzzard-6A455E05
kibuzzard-6A455E28: G***; kibuzzard-6A455E28
kibuzzard-6A455E35: G***; kibuzzard-6A455E35
kibuzzard-6A455ED1: G***; kibuzzard-6A455ED1
kibuzzard-6A455F32: G***; kibuzzard-6A455F32
kibuzzard-6A455FAF: G***; kibuzzard-6A455FAF
kibuzzard-6A455FB8: G***; kibuzzard-6A455FB8
kibuzzard-6A4560A1: G***; kibuzzard-6A4560A1
kibuzzard-6A4560DE: G***; kibuzzard-6A4560DE
kibuzzard-6A4561AC: G***; kibuzzard-6A4561AC
kibuzzard-6A6094FF: G***; kibuzzard-6A6094FF
kibuzzard-6A45612B: G***; kibuzzard-6A45612B
kibuzzard-6A45614A: G***; kibuzzard-6A45614A
kibuzzard-6A456096: G***; kibuzzard-6A456096
kibuzzard-6A456143: G***; kibuzzard-6A456143
kibuzzard-6A456164: G***; kibuzzard-6A456164
kibuzzard-6AD6CA76: G***; kibuzzard-6AD6CA76

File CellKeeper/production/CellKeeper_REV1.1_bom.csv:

Designator,Footprint,Quantity,Value,LCSC Part #
"1/2V1, 3V1, 5V1, GND1, GPIO44, GPIO45, GPIO46",BMS_Library__TestPoint_THTPad_D1.5mm_Drill1.0mm,7,TP,
"C1, C14, C31",Capacitor_THT__CP_Radial_D10.0mm_P5.00mm,3,680uF,C46550429
"C10, C104, C11, C13, C15, C16, C18, C2, C22, C23, C28, C29, C30, C34, C35, C36, C54, C60, C62, C64, C73, C74, C76, C77, C78, C79, C80, C81, C89, C91",Capacitor_SMD__C_0603_1608Metric,30,100nF,C14663
"C100, C101, C102, C44, C46, C47, C50, C51, C53, C56, C58, C59, C61, C63, C65, C75, C83, C84, C85, C86, C88, C90, C92, C93",Capacitor_SMD__C_0402_1005Metric,24,100n,C1525
"C103, C24, C25, C26, C27",Capacitor_SMD__C_0603_1608Metric,5,100pF,C14858
"C116, C17, C21, C3, C32, C4, C55, C6, C66, C8",Capacitor_SMD__C_0805_2012Metric,10,10uF,C440198
"C12, C33, C37, C48, C49, C5, C69, C7",Capacitor_SMD__C_0805_2012Metric,8,22uF,C45783
"C19, C20, C41, C42, C67, C96, C97, C98, C99",Capacitor_SMD__C_0603_1608Metric,9,1uF,C15849
"C38, C43, C45, C52, C68, C72, C82, C87",RP2350_80QFN_minimal__C_0402_1005Metric_small_pads,8,4.7u,C23733
"C39, C40, C70, C71",Capacitor_SMD__C_0402_1005Metric,4,15pF,C1548
C9,Capacitor_SMD__C_0603_1608Metric,1,4.7uF,C19666
"C94, C95",Capacitor_SMD__C_1206_3216Metric,2,1nF,C9196
"D1, D2, D24, D25, D26, D28, D29, D3, D30, D31, D4, D5, D6",Diode_SMD__D_SMB,13,SMB6.8CA,C78395
"D10, D27, D41, D46, D49, D9",LED_SMD__LED_0805_2012Metric,6,Red,C84256
"D11, D12, D15, D16, D20, D23, D37, D38, D42, D44, D47, D50",Diode_SMD__D_SMA,12,SS54,C22452
"D13, D17, D22, D33, D34, D45",LED_SMD__LED_0805_2012Metric,6,White,C34499
"D14, D19, D32, D35, D36, D43, D48, D7, D8",LED_SMD__LED_0805_2012Metric,9,Green,C2297
"D18, D21, D39, D40",Diode_SMD__D_SMC,4,SMCJ33CA,C224050
"FB1, FB3, FB5",Inductor_SMD__L_0603_1608Metric_Pad1.05x0.95mm_HandSolder,3,600R@100MHz,C1002
FB2,Capacitor_SMD__C_0603_1608Metric,1,120Ω@100MHz,C14709
"FL1, FL2",BMS_Library__FILTER-SMD_4P-L3.2-W2.5-BL,2,SDCW3225S-2-102TF,C192586
J1,BMS_Library__PhoenixContact_MC_1_5_4-G-3.81_1x04_P3.81mm_Horizontal_1.4mmPin,1,WJ15EDGRC-3.81-04P-14-00A, C7245
"J11, J19, J9",BMS_Library__USB_C_Receptacle_HRO_TYPE-C-31-M-12,3,USB_C_Receptacle_USB2.0_16P,C2765186
J14,BMS_Library__CONN_ZE05H-8DP-2H_HIR,1,ZE05H-8DP-2H,C17284895
J17,BMS_Library__CONN_173864-1_TYC_Empty_Pins,1,OEM HV Sense Connector,C573648
J2,BMS_Library__XFCN_T34008_M3_Terminal_Frame_PCB,1,T34008,C481446
J20,BMS_Library__CONN_SD-34912-001_02_MOL,1,OEM Connector,C587318
"J4, J5",Connector_RJ__RJ45_HCTL_HC-RJ45-5JA-2-2-Y,2,8P8C_LED_Shielded_x2,C3010546
J6,BMS_Library__S44BRAD1AK,1,S44B-RAD1AK,
"JP10, JP11, JP15, JP36, JP5, JP6",BMS_Library__J_0603_jumper,6,0r,C21189
"L1, L5",Inductor_SMD__L_Changjiang_FXL0630,2,6.8uh,C167221
"L2, L3",Inductor_SMD__L_Changjiang_FXL1040,2,22uh 5.5A,C475917
"L4, L6",RP2350_80QFN_minimal__L_pol_2016,2,3.3uh,C42411119
"Q1, Q2, Q3, Q4",BMS_Library__TDSON-8_5x6_,4,BSC0805LS,C534374
"R1, R100, R101, R11, R140, R16, R2, R29, R33, R35, R39, R40, R41, R96, R97, R98, R99",Resistor_SMD__R_0603_1608Metric,17,24k,C23352
"R10, R151, R152, R18, R24, R34, R36, R5",Resistor_SMD__R_0603_1608Metric,8,100k,C25803
"R102, R103, R104, R105, R106, R107, R108, R109, R110, R111, R112, R113, R114, R115, R116, R117, R118, R119, R120, R121, R122, R123, R124, R125",Resistor_SMD__R_1206_3216Metric,24,3M,C488822
"R12, R37, R38, R7",Resistor_SMD__R_0603_1608Metric,4,33R,C23140
"R126, R54, R68, R93",Resistor_SMD__R_0402_1005Metric,4,33r,C25105
"R127, R128, R70, R71",Resistor_SMD__R_0402_1005Metric,4,22R,C25092
"R129, R130, R131, R132, R135, R27, R53, R55, R56, R74, R92, R94, R95",Resistor_SMD__R_0402_1005Metric,13,1k,C11702
"R13, R14, R15, R17, R19, R20, R21, R25, R28, R3, R4, R42, R50, R51, R52, R75, R84",Resistor_SMD__R_0603_1608Metric,17,10k,C25804
"R133, R134, R141, R22, R23, R46, R47, R48, R49, R76, R8, R9",Resistor_SMD__R_0603_1608Metric,12,1k,C21190
"R136, R137",Resistor_SMD__R_0603_1608Metric,2,47r,C23182
"R138, R139, R143, R144, R153, R154, R45, R57, R66, R69, R72, R77, R79, R80, R81, R82, R83, R85, R89, R90",Resistor_SMD__R_0603_1608Metric,20,5.1k,C23186
R142,Resistor_SMD__R_0603_1608Metric,1,100R,C22775
"R145, R146",Resistor_SMD__R_1206_3216Metric,2,1M,C17927
"R155, R26, R78",Resistor_SMD__R_0402_1005Metric,3,3.3k,C25890
"R30, R73, R86",Resistor_SMD__R_0603_1608Metric,3,510r,C23193
"R31, R32",Resistor_SMD__R_1206_3216Metric,2,120r,C17909
"R43, R44",Resistor_SMD__R_0603_1608Metric,2,2.2k,C4190
"R87, R88",Resistor_SMD__R_0603_1608Metric,2,220r,C22962
"SW1, SW2, SW3, SW4",Button_Switch_SMD__SW_Push_1P1T_XKB_TS-1187A,4,TS-1187A-B-A-B,C318884
TR1,BMS_Library__HM2113ZNLT,1,HM2113ZNLT,C5730533
"U1, U11",Package_SO__SOIC-8_3.9x4.9mm_P1.27mm,2,UCC27524DR,C465729
"U10, U5",Package_SO__SOP-8_6.62x9.15mm_P2.54mm,2,ISO1050DUB,C16428
"U12, U13, U6, U7, U8, U9",Package_SO__SSOP-4_4.4x2.6mm_P1.27mm,6,LTV-217-B-G,C115450
"U14, U20",RP2350_80QFN_minimal__RP2350-QFN-80-1EP_10x10_P0.4mm_EP3.4x3.4mm_ThermalVias,2,RP2354B,C39843328
"U15, U4",BMS_Library__H0505S-1WR2,2,F0505S-1WR3,C7465182
U16,Package_SO__SOIC-8_3.9x4.9mm_P1.27mm,1,ISO1540,C179739
U17,Package_SO__TSSOP-10_3x3mm_P0.5mm,1,INA228,C5214669
"U18, U19",Package_SO__TSSOP-10_3x3mm_P0.5mm,2,ADS1115,C37593
U21,Package_SO__SOIC-8_3.9x4.9mm_P1.27mm,1,SP3485EN-L/TR,C8963
U22,Package_SO__SOIC-16_3.9x9.9mm_P1.27mm,1,AM26LV32EIDR,C527448
"U25, U26",Package_TO_SOT_SMD__SOT-223-3_TabPin2,2,TLV1117LV33DCYR,C15578
U3,Package_SO__TI_SO-PowerPAD-8_ThermalVias,1,TPS5430DDAR,C9864
"Y1, Y2",Crystal__Crystal_SMD_3225-4Pin_3.2x2.5mm,2,ABM8-272-T3,C20625731

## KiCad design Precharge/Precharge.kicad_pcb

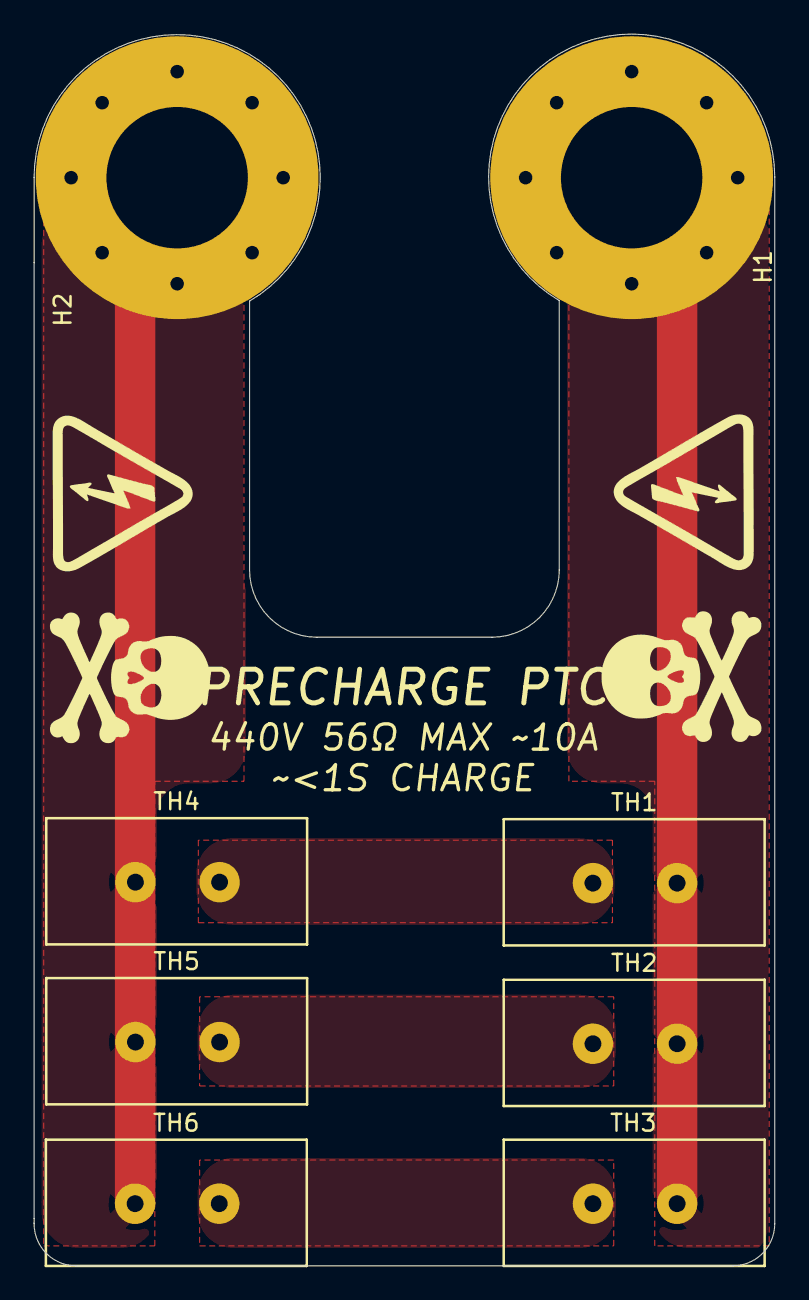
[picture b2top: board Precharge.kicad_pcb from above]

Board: 4 copper layers, 44.0 x 73.2 mm, 8 parts (0 on the bottom side), 5 nets.

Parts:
H1, H2: MountingHole_Pad; MountingHole__MountingHole_8.4mm_M8_Pad_Via
TH1, TH2, TH3, TH4, TH5, TH6: B59451C1130B070; BMS_Library__RV_Disc_D15.5mm_W7.5mm_P5.0mm

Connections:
/FC Neg: H2.1 (1_1), TH4.2, TH5.2, TH6.2
Drive Unit Neg: H1.1 (1_1), TH1.1, TH2.1, TH3.1
unnamed: TH1.2, TH4.1
unnamed: TH2.2, TH5.1
unnamed: TH3.2, TH6.1
